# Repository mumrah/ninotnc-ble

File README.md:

# NinoTNC BLE Expansion Board

This project brings robust and bi-directional Bluetooth connectivity to the
best amateur radio TNC on the market, the [NinoTNC](https://tarpn.net/t/nino-tnc/nino-tnc.html). This allows for the deployment of robust bi-directional APRS
at a low cost and in the DIY ham spirit.

The total cost for setting up an APRS mobile station using this project 
(excluding radio and antenna system) is around $80. 

* NinoTNC ($45 for DIY, more for pre-built)
* NinoBLE Expansion Board ($25 for pre-built, coming soon...)
* Custom TNC cable (free/cheap for DIY)
* APRS App (aprs.fi for iOS, APRSDroid for Android)

This project is experimental and should be considered as-is. The hardware and
firmware are open source licensed under the permissive MIT License.

# Features

* iOS and Android support
* Bi-directional APRS (receive and transmit)
* High-quality AFSK modulation, thanks to the NinoTNC
* USB powered using the USB-B connector on the NinoTNC
* Data logging to an on-board SD card
* Optional user-installed OLED display for packet information
* Pass-through mode for updating NinoTNC firmware

# Use Cases

## Mobile APRS

The most obvious and indeed the primary use case of this project. When set up
as described here, this board enables a very robust mobile APRS solution. Since
the NinoTNC is compatible with a wide range of 2m mobile radios (including
surplus commercial radios), the cost of the system can be kept low. 

The use of Bluetooth also allows for a "wireless" installation. There are no 
cables connected to the phone besides a charger. This allows for an arbitrary 
separation between the mobile phone and the TNC. The wireless range of the 
NinoBLE far exceeds any distance possible within a vehicle. 

## APRS Data Logging

The SD card located on the NinoBLE will log all packets sent and received.
This is quite useful when driving since logging in the APRS apps will
eventually roll off.

Each time the NinoBLE starts up, a new log file is created. This makes it
easy to find the most recent data, but also to retain the old data.

On-board data logging can also be useful for repeater operators who
occasionally have errant APRS traffic on their VHF repeaters. Logging
everything into the SD card makes it trivial to see who was accidentally
sending APRS traffic over the repeater.

## Portable APRS

If used with an HT, the NinoBLE can be used for portable APRS tracking. 
Since the APRS mobile apps use the phone's GPS, it is quite simple
to take this system into the field.

The same benefits of the Mobile APRS use case apply here. We can use 
inexpensive radios thanks to the high-quality DSP performed by the NinoTNC.

If the NinoBLE is equipped with the optional OLED screen, the NinBLE can be
used as a simple APRS receiver without a mobile phone.

## How it works

The primary function that this board adds to the NinoTNC is Bluetooth 
connectivity. There are many use cases for this besides APRS, but for now APRS 
is the focus of this project.

The expansion board is called the NinoBLE and connects physically to the NinoTNC
through the J5 header located under the USB to UART bridge. The NinoBLE board
replaces the USB to UART bridge that is normally installed on the TNC (at U4).

As KISS packets are received by the expansion board over Bluetooth, they are
decoded and forwarded to the UART interface. Similarly, when KISS data is
received over the UART, it is decoded and forwarded to the Bluetooth interface.

An optional SD card may be installed to capture the packets as they are sent andreceived.

## Hacking

The physical layout of the board is the only thing specific to the NinoTNC 
about this project. The electrical interface between the TNC and the expansion
board is 57600 baud UART and the data protocol used is KISS. This means that 
this project can be used to add Bluetooth to any KISS TNC that uses a UART.

The heart of this project is a RaspberryPi Pico W. Many of the GPIOs are unused,
so there is plenty of opportunity for expansion and tinkering.

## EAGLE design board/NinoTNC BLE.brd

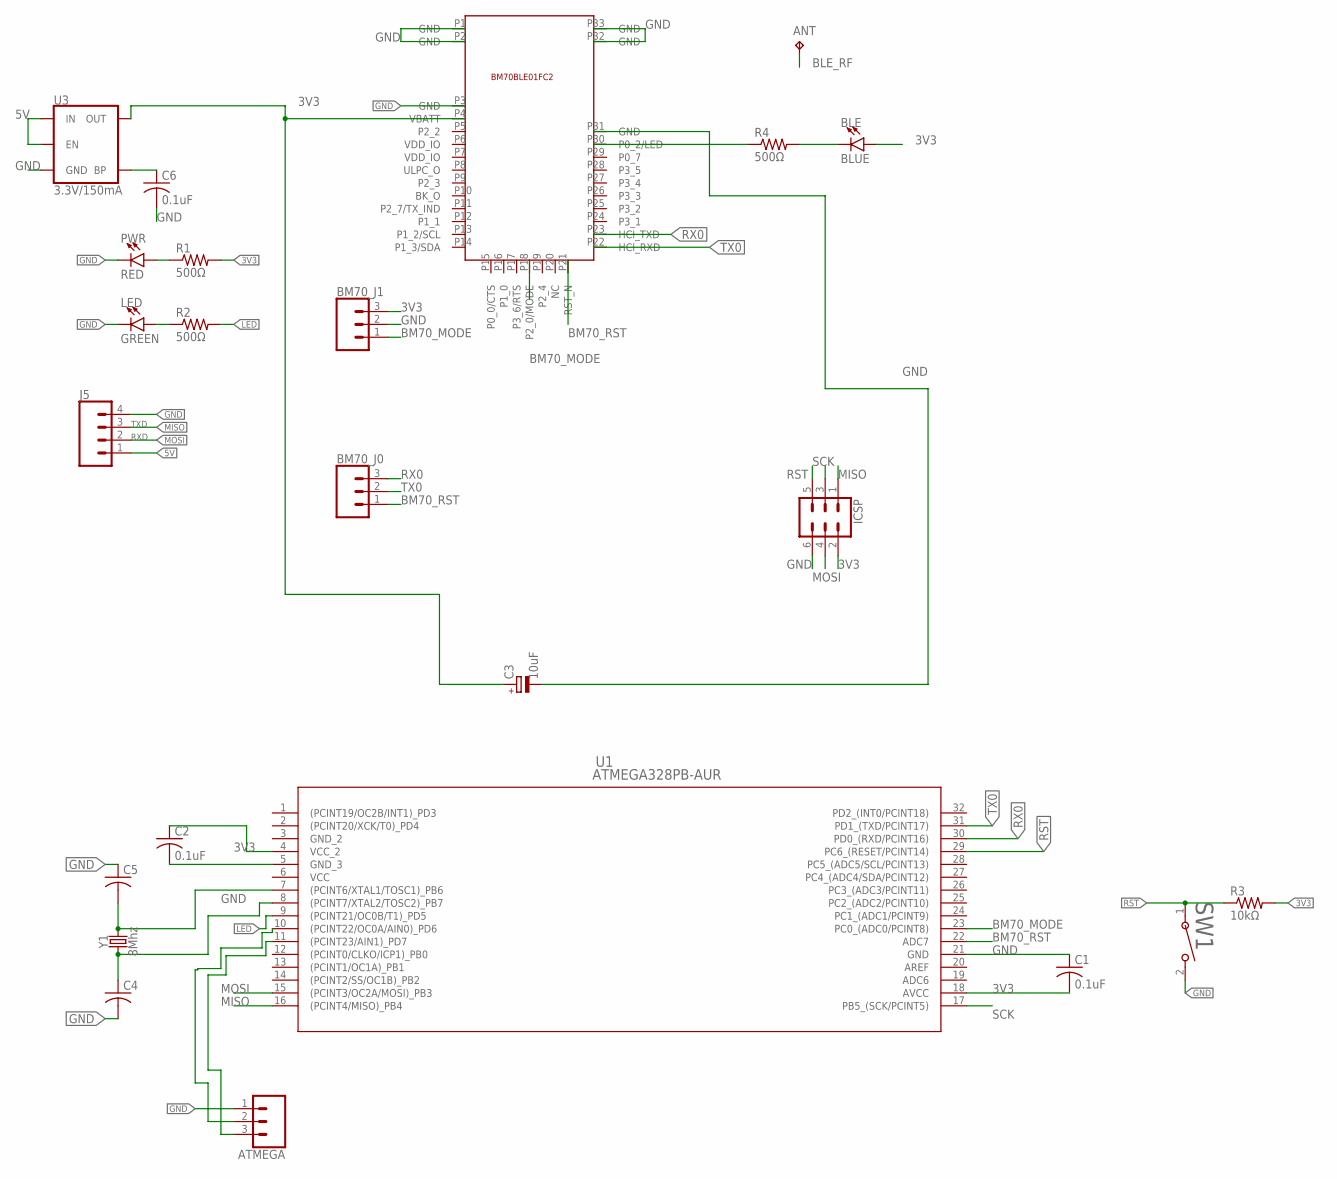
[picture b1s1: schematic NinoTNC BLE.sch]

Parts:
ANT: TPTP08SQ; TP08SQ
ATMEGA: CONN_03; 1X03
BLE: BLUE; LED-0603
BM70_J0, BM70_J1: CONN_03; 1X03
C1, C2, C6: 0.1uF; C0805
C3: 10uF; SMC_A
C4, C5: 22pF; C0805
ICSP: CONN_03X22X3_SILK_MALE_PTH; 2X3
J5: CONN_04; 1X04
LED: GREEN; LED-0603
PWR: RED; LED-0603
R1, R2, R4: 500Ω; M0805
R3: 10kΩ; R0805
SW1: EVQ-PE105K; EVQPE_5_PAN
U1: ATMEGA328PB-AUR; 32A_MCH
U3: 3.3V/150mA; SOT23-5
U$1: BM70BLE01FC2
Y1: 8Mhz; HC49U

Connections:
3V3: BLE.A, BM70_J1.3, C1.2, C2.1, C3.+, ICSP.2, R1.2, R3.2, U1.4 (VCC_2), U1.18 (AVCC), U3.5 (OUT), U$1.P4 (VBATT)
5V: J5.1, U3.1 (IN), U3.3 (EN)
BLE_RF: ANT.TP
BM70_MODE: BM70_J1.1, U1.23 (PC0_(ADC0/PCINT8)), U$1.P18 (P2_0/MODE)
BM70_RST: BM70_J0.1, U1.22 (ADC7), U$1.P21 (RST_N)
GND: ATMEGA.1, BM70_J1.2, C1.1, C2.2, C3.-, C4.2, C5.1, C6.2, ICSP.6, J5.4, LED.C, PWR.C, SW1.2, U1.5 (GND_3), U1.21 (GND), U3.2 (GND), U$1.P1 (GND), U$1.P2 (GND), U$1.P3 (GND), U$1.P31 (GND), U$1.P32 (GND), U$1.P33 (GND)
GND_2: U1.3 (GND_2)
LED: R2.2, U1.9 ((PCINT21/OC0B/T1)_PD5)
MISO: ICSP.1, J5.3, U1.16 ((PCINT4/MISO)_PB4)
MOSI: ICSP.4, J5.2, U1.15 ((PCINT3/OC2A/MOSI)_PB3)
unnamed: R4.1, U$1.P30 (P0_2/LED)
unnamed: BLE.C, R4.2
unnamed: ATMEGA.3, U1.11 ((PCINT23/AIN1)_PD7)
unnamed: C5.2, U1.7 ((PCINT6/XTAL1/TOSC1)_PB6), Y1.2
unnamed: C4.1, U1.8 ((PCINT7/XTAL2/TOSC2)_PB7), Y1.1
unnamed: PWR.A, R1.1
unnamed: LED.A, R2.1
unnamed: ATMEGA.2, U1.10 ((PCINT22/OC0A/AIN0)_PD6)
unnamed: C6.1, U3.4 (BP)
RST: ICSP.5, R3.1, SW1.1, U1.29 (PC6_(RESET/PCINT14))
RX0: BM70_J0.3, U1.30 (PD0_(RXD/PCINT16)), U$1.P23 (HCI_TXD)
SCK: ICSP.3, U1.17 (PB5_(SCK/PCINT5))
TX0: BM70_J0.2, U1.31 (PD1_(TXD/PCINT17)), U$1.P22 (HCI_RXD)
VCC: U1.6 (VCC)

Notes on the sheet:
TXD
RXD

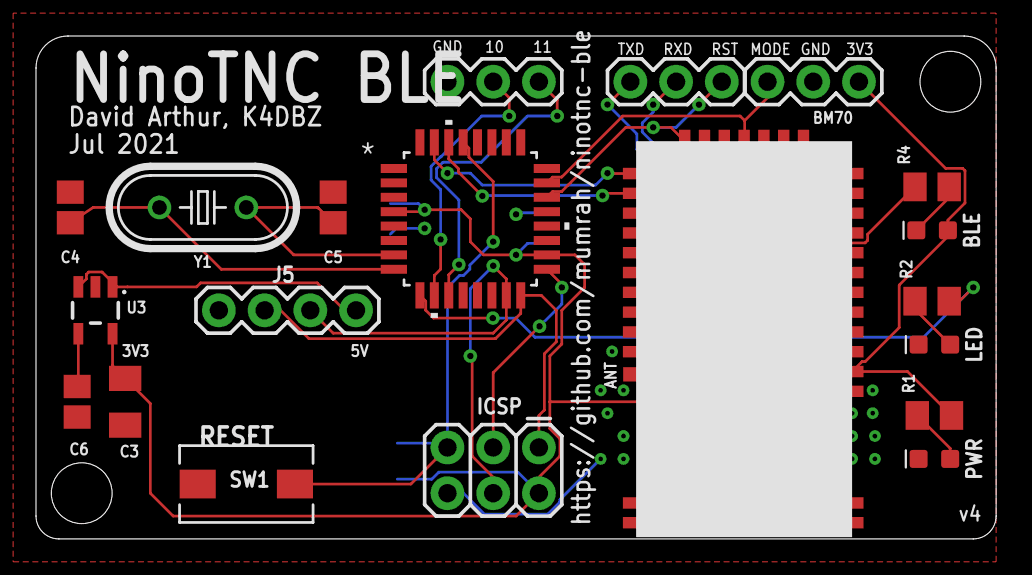
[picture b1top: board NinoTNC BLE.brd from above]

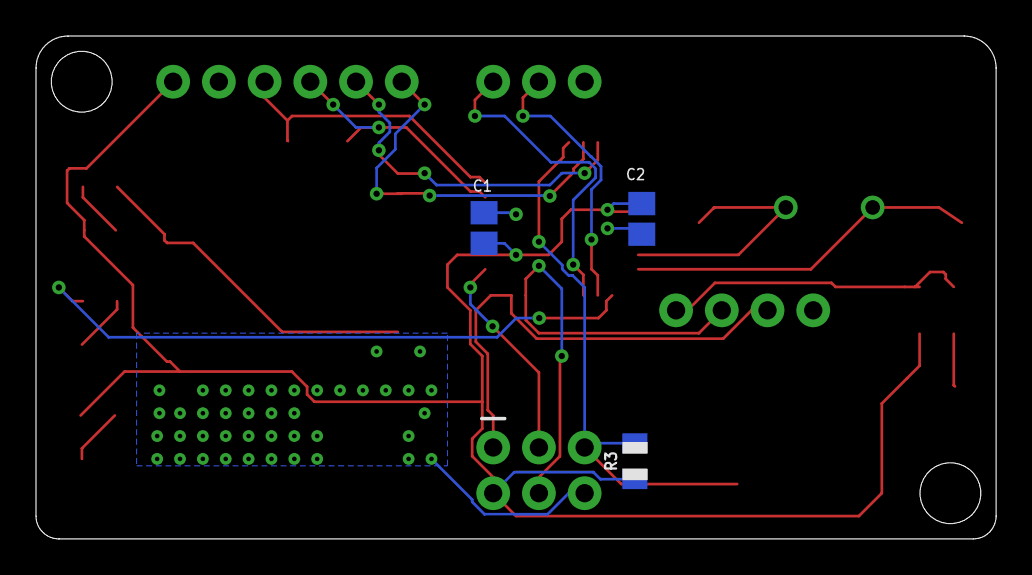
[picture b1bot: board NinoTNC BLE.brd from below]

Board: 2 copper layers, 53.3 x 27.9 mm, 24 parts (3 on the bottom side), 21 nets.

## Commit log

2020-10-13 Sort of working, converting to 328pb next
2020-10-15 Things are working
2020-10-16 Remove debug code
2020-10-16 minor cleanup
2020-11-27 Compiling
2020-12-01 Fix timing issues, got software serial working
    Still no data from BLE
2020-12-02 Fix several state related issues
2021-06-10 Cleanup
2021-06-11 Fix some timing issues in reading from BM70
2021-06-12 More reliable serial reading from BM70
2021-06-15 checkin before timer removal
2021-06-15 Things are working!
    One issue was not tying RST to MCLR on the NinoTNC. Occasionally, when
    programming the atemga, some magic sequence of bytes was sent that caused
    the NinoTNC to go into programming mode and the program got corrupted. Oops!
2021-06-15 Free up some memory
2021-06-15 Add some validation on BLE data
2021-06-18 Use interrupt for Nino TX as well
2021-06-22 Use F strings
2021-06-24 Async blinks
2021-06-24 Add GIT_REV macro
2021-06-24 Add dirty tag for uncommitted changes
2021-07-08 Don't forget the connection handle when getting a disconnect
    This (hopefully) fixes a bug where the board gets stuck in a reset/reconnect loop
2023-02-13 Add license (CC-BY-SA)
2023-02-13 Add PCB schematic and update readme
2025-01-18 1.0 updates
2025-01-18 Rename src directory
2025-01-18 add pcb
2025-01-18 Add YT video to README.md
2025-01-18 Move video down a bit
2025-01-19 fixup rev5 pcb files
2025-07-02 Get things working with Packet Commander
    * Only decode AX.25 from KISS DATA frames
    * Add mutex to protect buffers shared by the two cores
    * Add guard against infinite loop in AX.25 decoder
    * Allow multiple KISS frames to be buffered instead of just one

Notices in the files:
parts and their libraries:
SparkFun-LED: Licensing: Creative Commons ShareAlike 4.0 International - https://creativecommons.org/licenses/by-sa/4.0
COPYRIGHT: Copyright (C) 2018 Accelerated Designs. All rights reserved
